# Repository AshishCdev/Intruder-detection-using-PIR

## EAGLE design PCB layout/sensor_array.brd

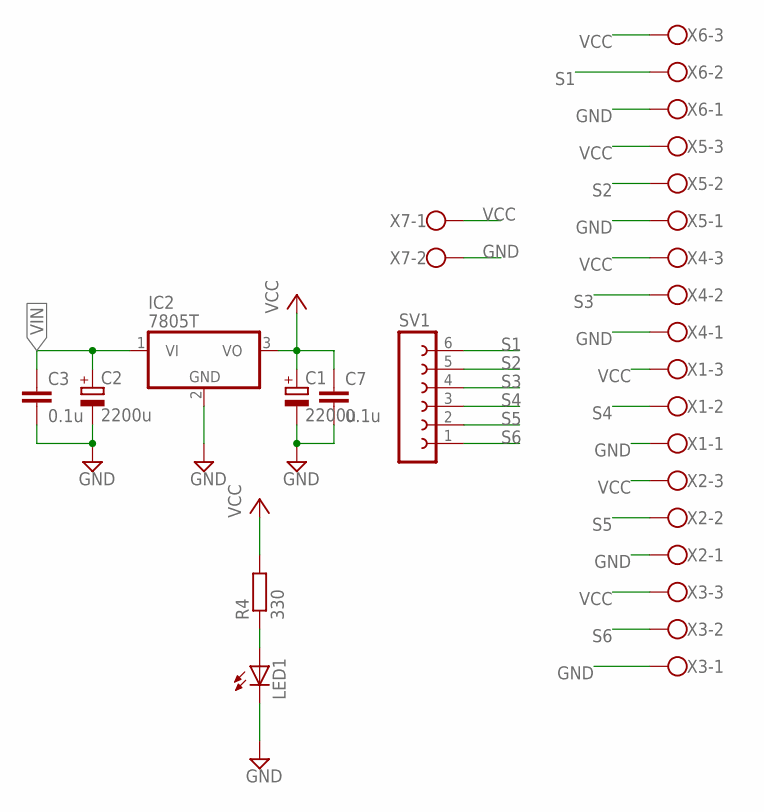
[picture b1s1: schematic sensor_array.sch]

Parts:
C1, C2: 2200u; E5-10,5
C3, C7: 0.1u; C5B3
IC2: 7805T; TO220H
LED1: LED5MM
R4: 330; 0207/10
SV1: FE06-1; FE06
X1, X2, X3, X4, X5, X6: W237-103
X7: W237-102

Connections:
GND: C1.-, C2.-, C3.2, C7.2, IC2.2 (GND), LED1.K (C), X1.1, X2.1, X3.1, X4.1, X5.1, X6.1, X7.2
unnamed: LED1.A, R4.1
S1: SV1.6, X6.2
S2: SV1.5, X5.2
S3: SV1.4, X4.2
S4: SV1.3, X1.2
S5: SV1.2, X2.2
S6: SV1.1, X3.2
VCC: C1.+, C7.1, IC2.3 (VO), R4.2, X1.3, X2.3, X3.3, X4.3, X5.3, X6.3, X7.1
VIN: C2.+, C3.1, IC2.1 (VI)

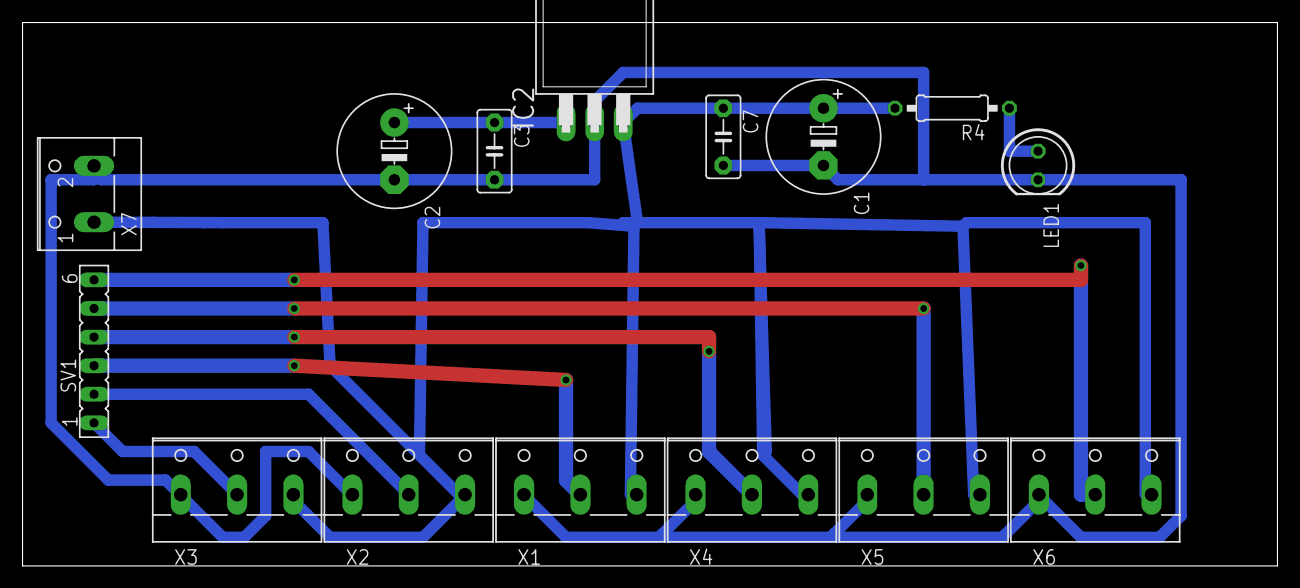
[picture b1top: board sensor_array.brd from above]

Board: 2 copper layers, 111.4 x 48.2 mm, 15 parts (0 on the bottom side), 10 nets.

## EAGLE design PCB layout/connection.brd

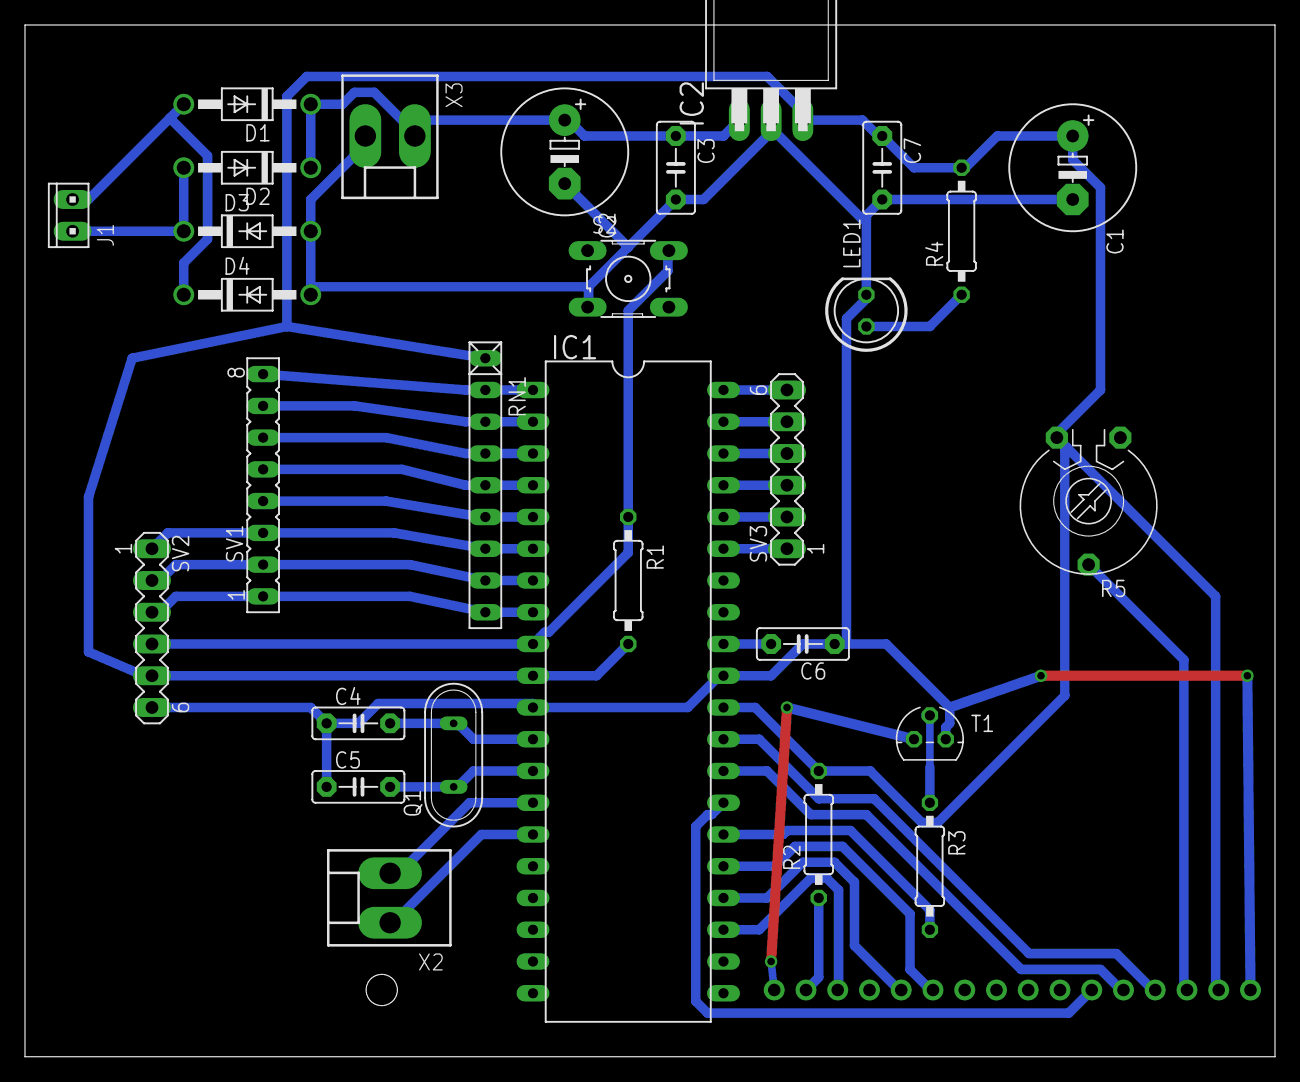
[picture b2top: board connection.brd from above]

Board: 2 copper layers, 100.0 x 82.5 mm, 30 parts (1 on the bottom side), 37 nets.

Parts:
C1, C2: 2200u; E5-10,5
C3, C7: 0.1u; C5B3
C4, C5: 22p; C5B2.5
C6: 0.1u; C5B2.5
D1, D2, D3, D4: 1N4004; DO41-10
DIS1: TUXGR_16X2_R2
IC1: MEGA16-P; DIL40
IC2: 7805T; TO220H
J1: 10X02MTA
LED1: LED5MM
Q1: 11.0592 Mz; QS
R1: 10k; 0207/10
R2, R4: 330; 0207/10
R3: 1k; 0207/10
R5: PT-10
RN1: 1k; RN-9
S2: B3F-10XX
SV1: FE08
SV2, SV3: MA06-1
T1: BC547; TO92
X2, X3: KK-156-2

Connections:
BLIGHT: IC1.26, R3.2
D0: IC1.1, RN1.2, SV1.8
D1: IC1.2, RN1.3, SV1.7
D2: IC1.3, RN1.4, SV1.6
D3: IC1.4, RN1.5, SV1.5
D4: IC1.5, RN1.6, SV1.4
D5: IC1.6, RN1.7, SV1.3, SV2.1
D6: IC1.7, RN1.8, SV1.2, SV2.2
D7: IC1.8, RN1.9, SV1.1, SV2.3
EN: DIS1.6, IC1.27
GND: C1.-, C2.-, C3.2, C4.1, C5.1, C6.1, C7.2, D3.A, D4.A, DIS1.1, IC1.11, IC1.31, IC2.2, LED1.K, S2.3, SV2.6, T1.1, X3.2
LD0: DIS1.11, IC1.25
LD1: DIS1.12, IC1.24
LD3: DIS1.14, IC1.23
unnamed: IC1.35, SV3.1
unnamed: C6.2, IC1.32
unnamed: C4.2, IC1.12, Q1.2
unnamed: C5.2, IC1.13, Q1.1
unnamed: D1.A, D4.C, J1.1
unnamed: DIS1.16, T1.3
unnamed: D2.A, D3.C, J1.2
unnamed: DIS1.15, R2.1
unnamed: R3.1, T1.2
unnamed: IC1.15, X2.1
unnamed: IC1.14, X2.2
unnamed: IC1.36, SV3.2
unnamed: LED1.A, R4.1
unnamed: IC1.37, SV3.3
unnamed: IC1.38, SV3.4
unnamed: IC1.39, SV3.5
unnamed: IC1.40, SV3.6
R: DIS1.4, IC1.29
R/W: DIS1.5, IC1.28
RS: DIS1.3, R5.3
RST: IC1.9, R1.1, S2.2, SV2.4
VCC: C1.+, C7.1, DIS1.2, IC1.10, IC1.30, IC2.3, R1.2, R2.2, R4.2, R5.2, RN1.1, SV2.5
VIN: C2.+, C3.1, D1.C, D2.C, IC2.1, X3.1

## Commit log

2016-01-07 Added Eagle layout
2016-01-25 corrected wrong connection at LCD terminal
2016-01-25 Added project code
